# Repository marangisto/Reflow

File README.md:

# Reflow
Reflow Oven Controller

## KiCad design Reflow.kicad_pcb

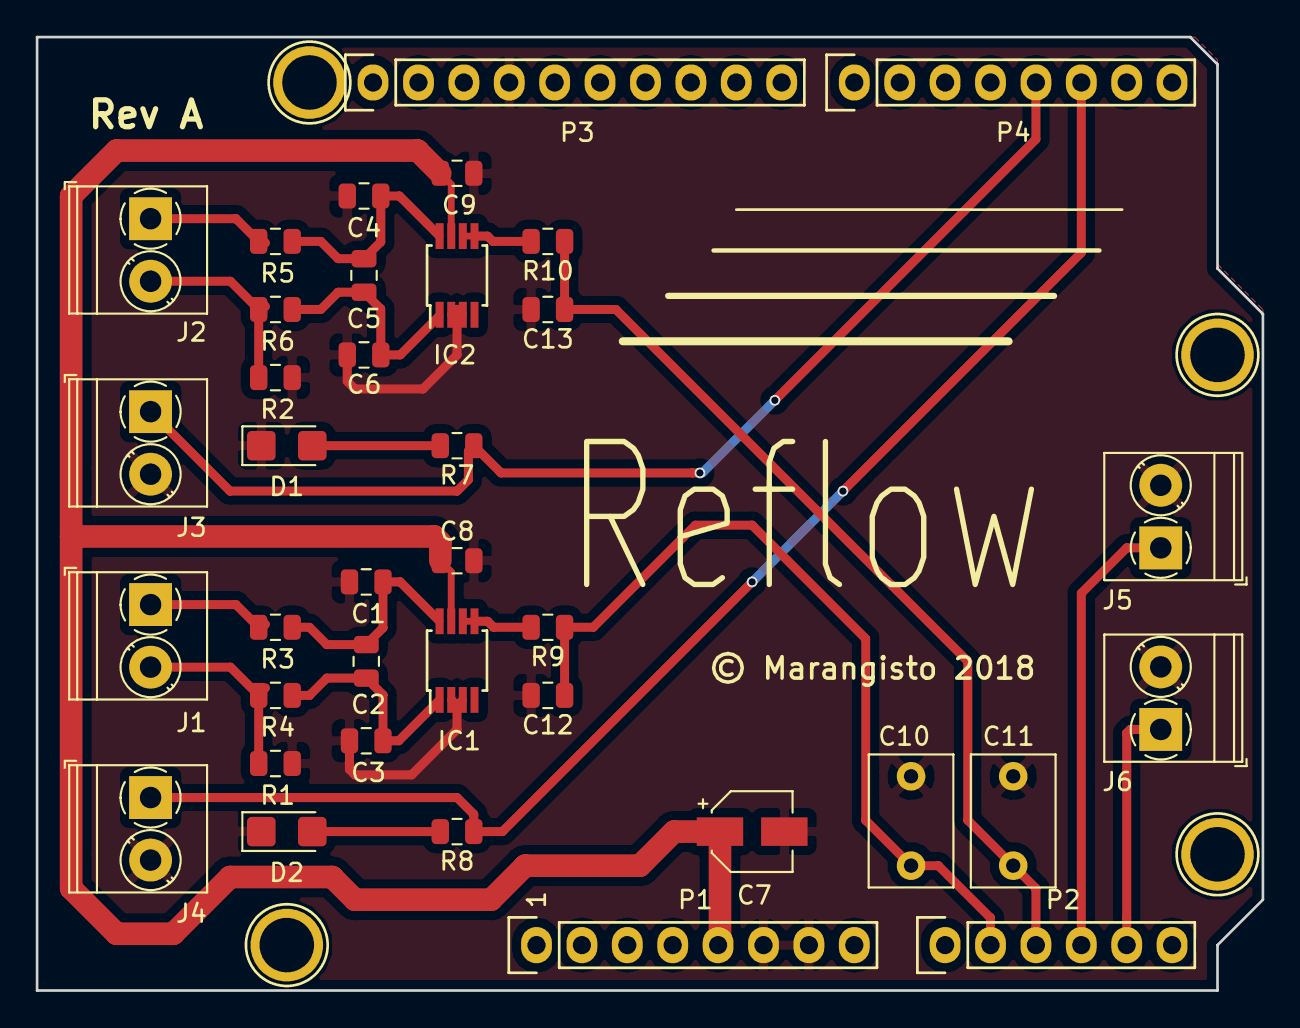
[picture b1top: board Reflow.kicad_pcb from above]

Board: 2 copper layers, 68.6 x 53.3 mm, 41 parts (0 on the bottom side), 20 nets.

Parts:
C1, C2, C3, C4, C5, C6, C8, C9, C12, C13: 100n; C_0805_2012Metric
C7: 10u; CP_Elec_4x5.8
C10, C11: 1u; C_Rect_L7.2mm_W4.5mm_P5.00mm_FKS2_FKP2_MKS2_MKP2
D1, D2: LED; LED_1206_3216Metric_Castellated
IC1, IC2: AD8495; MSOP-8_3x3mm_P0.65mm
J1, J2, J3, J4, J5, J6: Screw_Terminal_01x02; TerminalBlock_Phoenix_PT-1,5-2-3.5-H_1x02_P3.50mm_Horizontal
P1: Power; Socket_Strip_Arduino_1x08
P2: Analog; Socket_Strip_Arduino_1x06
P3: Digital; Socket_Strip_Arduino_1x10
P4: Digital; Socket_Strip_Arduino_1x08
P5, P6, P7, P8: CONN_01X01; Arduino_1pin
R1, R2: 1M; R_0805_2012Metric
R3, R4, R5, R6: 100; R_0805_2012Metric
R7, R8: 330; R_0805_2012Metric
R9, R10: 4k7; R_0805_2012Metric

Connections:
+5V: C7.1, C8.1, C9.1, IC1.7, IC2.7, P1.5
A1: C10.1, C12.1, P2.2, R9.1
A2: C11.1, C13.1, P2.3, R10.1
A3: J5.1, P2.4
A4: J6.1, P2.5
D2: J4.1, P4.6, R8.1
D3: J3.1, P4.5, R7.1
GND: C1.1, C3.2, C4.1, C6.2, C7.2, C8.2, C9.2, C10.2, C11.2, C12.2, C13.2, D1.1, D2.1, IC1.2, IC1.3, IC2.2, IC2.3, J3.2, J4.2, J5.2, J6.2, P1.6, P1.7, P3.4, R1.2, R2.2
unnamed: C1.2, C2.1, IC1.8, R3.1
unnamed: C2.2, C3.1, IC1.1, R4.1
unnamed: C4.2, C5.1, IC2.8, R5.1
unnamed: C5.2, C6.1, IC2.1, R6.1
unnamed: D1.2, R7.2
unnamed: D2.2, R8.2
unnamed: IC1.5, IC1.6, R9.2
unnamed: IC2.5, IC2.6, R10.2
unnamed: J1.1, R3.2
unnamed: J1.2, R1.1, R4.2
unnamed: J2.1, R5.2
unnamed: J2.2, R2.1, R6.2

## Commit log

2018-08-14 Added revision A of Reflow board.
2018-08-14 Added board rendering.
2018-08-15 Added low-pass filter on outputs.
2018-08-26 Added sheet for test results.
2018-08-26 Recorded first proper profile.

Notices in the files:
Reflow.kicad_pcb:
© Marangisto 2018
